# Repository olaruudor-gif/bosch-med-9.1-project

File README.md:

Started making a pcb for replacing the oem bosch ecu to make it tunable with tunerstudio and rusefi code.

Please feel free to use my files to continue my work.

No rights reserved.

Just a simple thanks, and I am happy!

It's all MAGIC

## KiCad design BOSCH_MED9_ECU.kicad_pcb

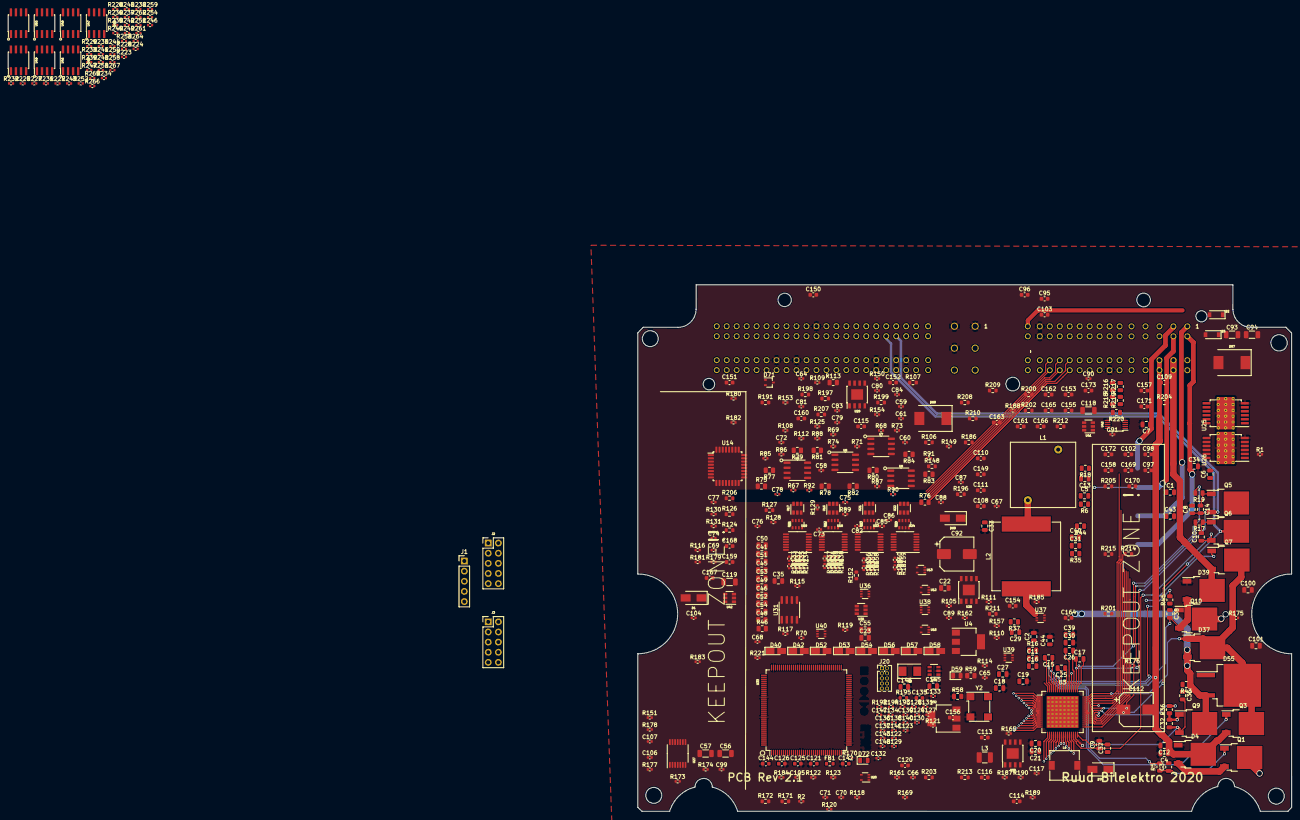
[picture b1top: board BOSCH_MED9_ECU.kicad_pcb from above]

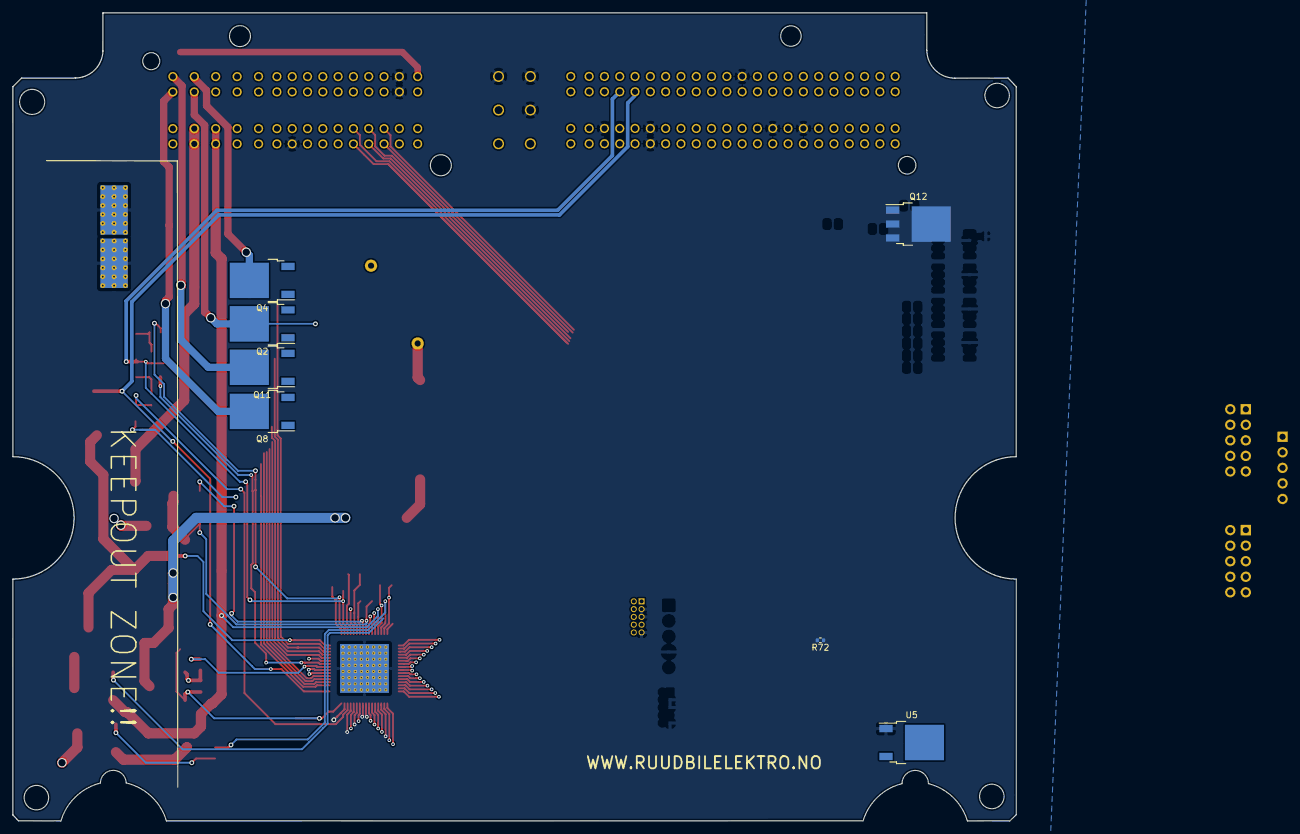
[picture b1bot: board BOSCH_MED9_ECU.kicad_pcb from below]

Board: 4 copper layers, 163.9 x 132.0 mm, 466 parts (7 on the bottom side), 339 nets.

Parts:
C1, C4, C6, C7, C8, C12, C30, C34, C39, C43: 4700pF; C_0805_2012Metric
C2, C9, C35, C36, C37, C44: 330pF; C_0805_2012Metric
C3, C5, C10, C11, C13, C14, C29, C31, C38, C40, C55: 1000pF; C_0805_2012Metric
C15, C16, C17, C25, C26: 0.33uF; C_0805_2012Metric
C18: 4.7uF; C_0805_2012Metric
C19, C20, C22, C23: 0.1uF; C_0805_2012Metric
C21: 1uF; C_0805_2012Metric
C27, C33: 220nF; C_0805_2012Metric
C32: 470pF; C_0805_2012Metric
C41, C45: 0.22uF; C_0805_2012Metric
C46, C49, C51, C53, C145: 100nF; C_0805_2012Metric
C48, C50, C52, C54: 10nF; R_0805_2012Metric
C56, C57, C93, C94, C118, C119: 10uF; C_1206_3216Metric
C58, C59, C60, C61, C65, C69, C127, C128, C129, C130, C131, C132, C133, C134, C136, C138, C139, C140, C141, C143, C147, C148: 100nF; C_0402_1005Metric
C64: 220pf; C_0402_1005Metric
C66, C67, C70, C71: 33nF; C_0402_1005Metric
C68: 1nF; C_0402_1005Metric
C72, C73, C74, C75, C76, C77, C78, C79, C80, C81, C82, C83, C84, C85, C86, C87, C88, C89, C90, C91, C99, C122, C137: 10nF; C_0402_1005Metric
C92: 220uF; CP_Elec_8x10
C95, C96, C97, C98, C114, C169, C171: 10nF; C_0603_1608Metric
C100, C101: 3.3nF; C_0805_2012Metric
C102, C103: 680pF; C_0603_1608Metric
C104, C105: 330p; C_0402_1005Metric
C106, C107: 47pF; C_0402_1005Metric
C108, C109, C111, C113, C115, C121, C135, C144: 1uF; C_0603_1608Metric
C110, C120, C142: 4.7uF; C_0603_1608Metric
C112: 68uF; CP_Elec_8x10
C116, C173: 100nF; C_0603_1608Metric
C117: 270pF; C_0402_1005Metric
C123, C124: 4.7pF; C_0402_1005Metric
C125, C126: 2.2uF; C_0603_1608Metric
C146: 22uF; C_0805_2012Metric
C149, C150, C151, C152, C153, C154, C155, C156, C157, C158, C159, C160, C161, C162, C163, C164, C165, C166, C167, C168, C170, C172: 1nF; C_0603_1608Metric
D1: SS54; D_SMA
D2, D3: B5819W; D_SOD-123
D4, D39: SBR10200CTL; TO-252-2
D37: FFD10UP20S; TO-252-2
D40, D42, D52, D53, D54, D56, D57, D58: 5.7V; D_MicroMELF_Handsoldering
D55: STTH802G-TR; TO-263-2
D59: LED_Small; LED_0805_2012Metric
D67, D68: SM15T33CA; D_SMC
D69, D70: D_Schottky; D_SMA
D71: PESD1CAN-UX; SOT-323_SC-70
D72: LED GREEN; LED_0805_2012Metric
FB1: FILTER; R_0603_1608Metric
J1: Conn_01x05; PinHeader_1x05_P2.54mm_Vertical
J2, J3: Conn_01x10; PinHeader_2x05_P2.54mm_Vertical
J20: Conn_02x05_Odd_Even; PinHeader_2x05_P1.27mm_Vertical
L1: 6uH; L_Radial_L16.1mm_W16.1mm_Px7.62mm_Py12.70mm_Pulse_LP-44
L2: 10uH; L_Vishay_IHLP-6767
L3: 2.2uF; L_1210_3225Metric
L4: 10uF; L_7.3x7.3_H3.5
Q1, Q2, Q3, Q4, Q5, Q6, Q7, Q8, Q9, Q10, Q11: BUK9230-100B; TO-252-2
Q12: RFD16N05LSM9A; TO-252-3_TabPin2
R1, R2: 10k; R_0402_1005Metric
R5, R6, R16, R17, R18, R19, R35, R36, R37, R44, R45, R58: 10R; R_0805_2012Metric
R43, R46: 5.1R; R_0805_2012Metric
R59: 1k; R_0805_2012Metric
R67, R68, R69, R70, R71, R72, R73, R74, R85, R86, R87, R88, R89, R90, R91, R92, R105, R111, R115, R117, R121, R122, R149, R185, R187, R188, R192, R193, R226, R231, R232, R235, R236, R237, R238, R239, R240, R241, R242, R243, R244, R245, R246, R247, R248, R249, R250, R251, R258, R259, R261, R262, R264, R265, R266, R267: 10K; R_0402_1005Metric
R75: 0R; R_0805_2012Metric
R76, R220: DNP; R_0805_2012Metric
R77, R78, R79, R80, R81, R82, R83, R84: 100R; R_0805_2012Metric
R106: 220R; R_0603_1608Metric
R107: 82.5R; R_0603_1608Metric
R108, R116, R119, R175, R176, R181, R182, R194: 100K; R_0402_1005Metric
R109, R125, R128, R129, R130, R131, R150, R151, R153, R154, R177, R178: 470K; R_0402_1005Metric
R110: 21.6K; R_0402_1005Metric
R112, R221: 4.7K; R_0402_1005Metric
R113: 61.9R; R_0805_2012Metric
R114, R123: 6.8K; R_0402_1005Metric
R118, R120, R132, R133, R134, R135, R136, R137, R138, R139, R155, R156, R157, R158, R159, R160, R161, R162, R222, R223, R224, R225, R227, R228, R229, R230, R233, R234, R252, R253, R254, R255: 1K; R_0402_1005Metric
R124, R126, R127, R152: 2.7K; R_0603_1608Metric
R140, R141, R142, R143, R144, R145, R146, R147, R163, R164, R165, R166, R167, R168, R169, R170: 1.5K; R_0402_1005Metric
R148: 39K; R_0603_1608Metric
R171, R172: 10K; R_0603_1608Metric
R173, R174: 22k; R_0402_1005Metric
R179, R180, R189: 12K; R_0402_1005Metric
R183, R184: 33K; R_0402_1005Metric
R186: 10Hms; R_0603_1608Metric
R190: 68K; R_0402_1005Metric
R191: 120R; R_0603_1608Metric
R195: 680R; R_0603_1608Metric
R196, R197, R198, R199, R200, R201, R202, R203, R204, R205: 2.2K; R_0603_1608Metric
R206, R207, R208, R209, R210, R211, R212, R213, R214, R215: 3.3K; R_0603_1608Metric
R216, R217, R218, R219: 5K; R_0805_2012Metric
RN1, RN2, RN3, RN4: 10K; R_Array_Convex_4x0603
U1: BOSCH_94-PIN; BOSCH_94_PIN
U2: BOSCH_60-PIN; BOSCH_60_PIN
U3: MC33816; HTQFP-64-1EP_10x10mm_P0.5mm_EP8x8mm_Mask4.4x4.4mm_ThermalVi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
U4: AMS1117-3.3; SOT-223
U5: NCP1117-5.0_TO252; TO-252-2
U6, U7, U8, U9: TC4427; SO-8_3.9x4.9mm_P1.27mm
U12, U13, U15, U20: TS5A3166DCKR; SOT-353_SC-70-5
U14: CJ125; LQFP-32_7x7mm_P0.8mm
U16, U17, U21, U22, U34, U35, U41, U42: SRV05-4; SOT-23-6
U18, U19, U23, U24, U27: MCP6004T-I/ST; TSSOP-14_4.4x5mm_P0.65mm
U25, U26: IFX9201SGAUMA1; Infineon_PG-DSO-12-9_ThermalVias
U28, U29: TLS115; Infineon_PG-DSO-8-43
U30: LMR14020; Infineon_PG-DSO-8-43
U31: TJA1051T-3; SOIC-8_3.9x4.9mm_P1.27mm
U32: AMS1117-3.3; SOT-223-3_TabPin2
U33: STM32F767ZIT6; LQFP-144_20x20mm_P0.5mm
U36, U37, U38, U39, U40: 74LVC2G17; SOT-363_SC-70-6
U43: MAX9924; MSOP-10_3x3mm_P0.5mm
U44, U45, U46, U47, U48, U49, U50: 511-VNLD5160TR-E; PowerIntegrations_SO-8
X1: 8MHz; Crystal_SMD_5032-2Pin_5.0x3.2mm
Y2: 1MHz; Oscillator_SMD_Diodes_FN-4Pin_7.0x5.0mm

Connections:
+3V3: C23.1, C55.1, C120.1, C127.2, C128.2, C129.2, C130.2, C131.2, C132.2, C133.2, C134.2, C136.2, C138.2, C139.2, C140.2, C141.2, C144.2, C145.1, C146.1, D72.2, FB1.1, J3.4, J20.1, R1.1, R2.1, R171.2, R172.2, R173.2, R193.2, R221.1, U3.17, U25.2, U26.2, U27.4, U31.5, U32.2, U33.6, U33.17, U33.30, U33.39, U33.52, U33.62, U33.72, U33.84, U33.95, U33.108, U33.121, U33.131, U33.143, U33.144, Y2.4
+5V: C22.1, C66.2, C80.1, C81.1, C90.1, C91.1, C117.1, C118.1, C119.1, C142.2, C143.1, C173.1, J3.1, L4.2, R76.1, R115.2, R126.2, R127.2, R185.2, R188.2, R190.2, R196.1, R197.1, R198.1, R199.1, R200.1, R201.1, R202.1, R203.1, R204.1, R205.1, RN4.1, U3.21, U12.5, U13.5, U14.5, U14.18, U14.19, U15.2, U15.5, U16.5, U17.5, U18.4, U19.4, U20.2, U20.5, U21.5, U22.5, U23.4, U24.4, U28.5, U31.3, U32.3, U35.5, U36.5, U37.5, U38.5, U39.5, U40.5, U41.5, U42.5, U43.10
/5V1: C109.1, U2.37, U28.1
/5V2: C115.1, U1.58, U1.63, U1.80, U2.26, U29.9
/5V_Ext: C58.1, C59.1, C60.1, C61.1, R75.1, R76.2, R242.2, R243.1, R244.2, R245.1, R246.2, R247.1, R248.2, R249.1, R250.2, R251.1, R264.2, R265.1, R266.2, R267.1, U6.6, U7.6, U8.6, U9.6
/12V: C67.2, C108.1, C111.1, D69.1, J3.3, L3.1, R148.2, R186.1, U14.30, U28.7, U28.8
/12V_FROM_MAIN_RELAY: C92.1, C93.2, C94.2, D2.1, D3.1, D67.1, J3.8, U25.4, U26.4
/12V_IGN: D68.1, D69.2
/12V_SWITCH_PROT: C56.1, D1.1, U5.3
/AC-COMP: R251.2, U48.6
/AC-REQ: C154.1, R201.2, R211.2
/ACC-PEDAL-1: R150.1, RN3.1, U1.79
/ACC-PEDAL-2: R154.1, RN4.4, U1.57
/ADC8_BIAS: U15.4, U33.77
/ADC14_BIAS: U20.4, U33.11
/ADC/ADC_11_MCU: R157.2, R165.1
/AN-TEMP-1: R124.1, RN2.1
/AN-VOLT-2: J1.4, R151.1, RN3.3
/AN-VOLT-3: R130.1, RN1.3
/AN_VOLT_1: R131.1, RN1.4
/AnOut1: R132.2, R140.1, U33.26
/AnOut2: R133.2, R141.1, U33.27
/AnOut3: R134.2, R142.1, U33.28
/AnOut4: R135.2, R143.1, U33.29
/AnOut5: R136.2, R144.1, U33.47
/AnOut6: R137.2, R145.1, U33.46
/AnOut7: R138.2, R146.1, U33.45
/AnOut8: R139.2, R147.1, U33.44
/AnOut9: R155.2, R163.1, U33.43
/AnOut10: R156.2, R164.1, U33.42
/AnOut12: R158.2, R166.1, U33.41
/AnOut13: R159.2, R167.1, U33.40
/AnOut14: R160.2, R168.1, U33.37
/BOOST_VALVE: R243.2, U44.6
/BRAKE-PEDAL: C149.1, R196.2, R206.2
/BRAKE-PEDAL-2: C156.1, R203.2, R213.2
/BRAKE-RELAY: R244.1, U1.31, U45.8
/CAM_1: C157.1, R204.2, R214.2
/CAM_1_MCU: U33.96, U40.6
/CAM_2: C158.1, R205.2, R215.2
/CAM_2_MCU: U33.93, U40.4
/CANH: D71.2, R191.1, U1.68, U1.90, U31.7
/CANL: D71.1, R191.2, U1.67, U1.89, U31.6
/CLT_SENSOR: R126.1, RN1.1
/CLUTCH-PEDAL: C150.1, R197.2, R207.2, U1.41
/COIL-1: R82.1, R89.2, U2.58
/COIL-2: R77.1, R85.2, U2.43
/COIL-3: R80.1, R87.2, U2.56
/COIL-4: R78.1, R92.2, U2.41
/COIL-5: R81.1, R88.2, U2.57
/COIL-6: R79.1, R86.2, U2.42
/COIL-7: R83.1, R90.2
/COIL-8: R84.1, R91.2
/CRANK: C172.1, R221.2, U33.86, U43.7
/CRIUSE-SET: C152.1, R199.2, R209.2
/CRNK+: R217.2, U2.51
/CRNK-: R216.2, U2.36
/CRUISE-SW: C153.1, R200.2, R210.2
/CS_LSU: U14.17, U33.66
/DI1: U33.54, U36.6
/DI2: U33.55, U36.4
/DI3: U33.97, U37.6
/DI4: U33.49, U37.4
/DI5: U33.56, U38.6
/DI6: U33.57, U38.4
/DI7: U33.50, U39.6
/DI8: U33.53, U39.4
/DIGITAL_GP: C155.1, R202.2, R212.2
/E-Throttle/ETB_1_DIR: U25.1, U33.99
/E-Throttle/ETB_1_DIS: R171.1, U25.11, U33.124
/E-Throttle/ETB_1_PWM: U25.12, U33.100
/E-Throttle/ETB_2_DIR: U26.1, U33.98
/E-Throttle/ETB_2_DIS: R172.1, U26.11, U33.122
/E-Throttle/ETB_2_PWM: U26.12, U33.123
/ECT-SENSOR-2: R152.1, RN4.3, U1.12
/ENGINE-RELAY: R246.1, U1.69, U46.8
/ETB_1+: C95.2, U2.15, U25.5
/ETB_1-: C96.1, U2.30, U25.7
/ETB_2+: C97.2, U26.5
/ETB_2-: C98.1, U26.7
/EXH-CAM: D3.2, R249.2, U47.6
/FAN_CONTROL: R247.2, U46.6
/FUEL-PUMP: R245.2, U45.6
/FUEL-PUMP+: C8.1, C14.2, C17.1, Q5.3, U1.32, U3.51
/FUEL-PUMP-: C6.1, Q6.2, U1.33, U3.33
/GPIOF_2: J2.2, U33.12
/HGATE-LSU: Q12.1, R121.2, U14.4, U33.64
/IAT-SENSOR: U1.13, U2.13
/IAT_SENSOR: R127.1, RN2.3
/IGN1: R67.1, U6.2, U33.115
/IGN2: R72.2, U6.4, U33.114
/IGN3: R68.1, U7.2, U33.119
/IGN4: R71.2, U7.4, U33.118
/IGN5: R69.1, U8.2, U33.117
/IGN6: R74.2, U8.4, U33.116
/IGN7: R73.1, U9.2, U33.92
/IGN8: R70.2, U9.4, U33.91
/INJECTOR-1: C7.1, Q4.2, U2.2, U3.38
/INJECTOR-2: C1.1, Q2.2, U2.17, U3.37
/INJECTOR-3: C34.1, Q8.2, U2.16, U3.36
/INJECTOR-4: C43.1, Q11.2, U2.1, U3.35
/INJECTOR_DRIVERS/INJ_IN_1: R222.2, U33.140
/INJECTOR_DRIVERS/INJ_IN_2: R223.2, U33.141
/INJECTOR_DRIVERS/INJ_IN_3: R233.2, U33.142
/INJECTOR_DRIVERS/INJ_IN_4: R234.2, U33.1
/INJECTOR_DRIVERS/INJ_IN_5: R224.2, U33.2
/INJECTOR_DRIVERS/INJ_IN_6: R225.2, U33.3
/INJECTOR_DRIVERS/INJ_IN_7: R227.2, U33.137
/INJECTOR_DRIVERS/INJ_IN_8: R228.2, U33.139
/INJECTOR_DRIVERS/LS_IN_9: R229.2, U33.127
/INJECTOR_DRIVERS/LS_IN_10: R230.2, U33.128
/INJECTOR_DRIVERS/LS_IN_11: R252.2, U33.125
/INJECTOR_DRIVERS/LS_IN_12: R253.2, U33.126
/INJECTOR_DRIVERS/LS_IN_13: R254.2, U33.129
/INJECTOR_DRIVERS/LS_IN_14: R255.2, U33.132
/INJECTOR_PWR_BNK_1_1: C4.1, C11.2, C12.1, C16.2, D4.2, Q3.3, U2.33, U2.48, U3.60
/INJECTOR_PWR_BNK_2_1: C26.2, C29.2, C30.1, C39.1, D39.2, Q7.3, U2.32, U2.47, U3.54
/INJECTOR_PWR_BNK_3_1: U2.31, U2.46
/INT-CAM: D2.2, R266.1, U50.8
/L9637_L: J3.7, U33.13
/LSU1_HEATER: Q12.2, R114.1, U1.51
/LSUIA1: R109.1, R113.1, U1.81, U14.2
/LSUIP1: R113.2, U1.60, U14.32
/LSUUN1: C64.1, R108.2, U1.82, U14.31
/LSUVM1: R107.1, U1.61, U14.20
/LS_OUT_1: R242.1, U44.8
/LS_OUT_2: R267.2, U50.6
/LS_OUT_3: R265.2, U49.6
/LS_OUT_4: R250.1, U48.8
/LS_OUT_5: R248.1, U47.8
/MAF-SENSOR: R153.1, RN3.4, U1.85
/MAP-SENSOR: R128.1, RN1.2, U1.38
/MCU/D+: U33.104, U34.1
/MCU/D-: U33.103, U34.3
/MCU/NRST: J20.10, R193.1, U33.25
/MCU/PB6: U31.1, U33.136
/MCU/PB12: U31.4, U33.73
/MCU/SWCLK: J20.4, U33.109
/MCU/SWDIO: J20.2, U33.105
/MCU/Vbus: C148.2, U33.101, U34.5
/MCU/shield: C147.1, R194.1
/O2_input_CJ125/4.2_4.9: R105.2, U12.4, U13.4, U33.65
/O2_input_CJ125/COM: R106.1, R107.2, U12.2
/O2_input_CJ125/NO: R106.2, U12.1, U14.8
/POWER SUPPLY/5V_SENSOR_1_PG: R185.1, U28.4
/PT2000/BANK1_BAT: C3.2, C15.2, D4.3, Q1.3, U3.63
/PT2000/BANK2_BAT: C25.2, C38.2, D39.3, Q10.3, U3.57
/PT2000/CLK: U3.1, Y2.3
/PT2000/G_HB1_BAT: R5.2, U3.62
/PT2000/G_HB1_BST: R16.2, U3.59
/PT2000/G_HB2_BAT: R45.2, U3.56
/PT2000/G_HB2_BST: R37.2, U3.53
/PT2000/G_LS6: R19.2, U3.50
/PT2000/G_L_BOOST: R36.2, U3.41
/PT2000/G_L_INJ1: R18.2, U3.47
/PT2000/G_L_INJ2: R6.2, U3.46
/PT2000/G_L_INJ3: R35.2, U3.45
/PT2000/G_L_INJ4: R44.2, U3.44
/PT2000/G_PUMP: R17.2, U3.42
/PT2000/P_B1_SENSE: C2.1, C5.1, C13.1, Q2.3, Q4.3, U3.26
/PT2000/P_B2_SENSE: C31.1, C40.1, C44.1, Q8.3, Q11.3, U3.28
/PT2000/P_SENSE_BOOST: C32.1, C35.1, C36.2, C37.2, C41.2, C45.2, C46.2, C48.2, C49.2, C50.2, C51.2, C52.2, C53.2, C54.2, Q9.3, U3.32
/PT2000/P_SENSE_PUMP: C9.1, C10.1, Q6.3, U3.30
/PT2000/VCC2P5: C20.1, C21.1, U3.20
/PT2000/VCCP: C18.1, C19.1, U3.40
/PT2000/Vbat: C27.1, L1.2, Q1.2, Q5.2, Q10.2, U3.39
/PT2000/Vboost: C41.1, C45.1, C46.1, C48.1, C49.1, C50.1, C51.1, C52.1, C53.1, C54.1, D37.1, D37.2, D40.1, D55.2, Q3.2, Q7.2, R46.1, U3.48
/PT2000/Vbuck: D37.3, D55.3, L2.1, Q9.2, R43.1
/PT2000/Vpwr: C33.1, L1.1, L2.2
/SCK-LSU: U14.13, U33.74
/SD_CS: J1.5, U33.18
/SI-LSU: U14.15, U33.76
/SO-LSU: R119.2, U14.14, U33.75
/SPEED-SIGNAL: C151.1, R198.2, R208.2, U1.71
/SPI5_MISO: J1.1, U33.20
/SPI5_MOSI: J1.2, U33.21
/SPI5_SCK: J1.3, U33.19
/STARTER_RELAY: U1.52, U1.74
/THERMOSTAT: R264.1, U1.8, U49.8
/TPS_MAIN: R125.1, RN2.2
/TPS_SUB: R129.1, RN2.4
/UA-LSU: R122.1, R123.1, U33.36
/UART4_RX: J2.8, U33.112
/UART4_TX: J2.10, U33.111
/UART7_CTS: J2.6, U33.63
/UART7_RTS: J2.4, U33.60
/UART7_RX: J3.9, U33.59
/UART7_TX: J3.10, U33.58
/UBHR: U1.3, U1.5, U1.6
/UBR_MCU: R161.2, R169.1, U33.34
/UR-LSU: C70.1, R118.1, U33.35
/USART3_RX: J3.5, U33.70
/USART3_TX: J3.6, U33.69
/Vref: C121.2, C122.2, R162.2, R170.1, U33.32
/knock/FILTERED_1: C104.2, U27.6, U27.7, U33.14
/knock/FILTERED_2: C105.2, U27.8, U27.9, U33.15
/knock/V_mid: C99.2, R173.1, R174.1, U27.3, U27.12
GND: C1.2, C2.2, C4.2, C6.2, C7.2, C8.2, C9.2, C12.2, C18.2, C19.2, C20.2, C21.2, C22.2, C23.2, C27.2, C30.2, C33.2, C34.2, C35.2, C39.2, C43.2, C44.2, C55.2, C56.2, C57.2, C58.2, C59.2, C60.2, C61.2, C64.2, C66.1, C67.1, C68.2, C69.1, C70.2, C71.1, C72.2, C73.2, C74.2, C75.2, C76.2, C77.2, C78.2, C79.2, C80.2, C81.2, C82.2, C83.2, C84.2, C85.2, C86.2, C87.2, C88.2, C89.2, C90.2, C91.2, C92.2, C93.1, C94.1, C95.1, C96.2, C97.1, C98.2, C99.1, C102.1, C103.1, C106.1, C107.1, C108.2, C109.2, C110.2, C111.2, C112.2, C113.2, C114.2, C115.2, C118.2, C119.2, C120.2, C121.1, C122.1, C123.2, C124.2, C125.2, C126.2, C127.1, C128.1, C129.1, C130.1, C131.1, C132.1, C133.1, C134.1, C135.1, C136.1, C137.1, C138.1, C139.1, C140.1, C141.1, C142.1, C143.2, C144.1, C145.2, C146.2, C147.2, C148.1, C149.2, C150.2, C151.2, C152.2, C153.2, C154.2, C155.2, C156.2, C157.2, C158.2, C159.2, C160.2, C161.2, C162.2, C163.2, C164.2, C165.2, C166.2, C167.2, C168.2, C169.1, C171.2, C172.2, C173.2, D4.1, D39.1, D59.1, D67.2, D68.2, D70.2, D71.3, J3.2, J20.3, J20.5, J20.9, Q12.3, R58.1, R67.2, R68.2, R69.2, R70.1, R71.1, R72.1, R73.2, R74.1, R85.1, R86.1, R87.1, R88.1, R89.1, R90.1, R91.1, R92.1, R105.1, R117.1, R119.1, R121.1, R122.2, R125.2, R128.2, R129.2, R130.2, R131.2, R140.2, R141.2, R142.2, R143.2, R144.2, R145.2, R146.2, R147.2, R149.2, R150.2, R151.2, R153.2, R154.2, R163.2, R164.2, R165.2, R166.2, R167.2, R168.2, R169.2, R170.2, R174.2, R187.2, R189.2, R192.2, R194.2, R195.1, R226.1, R231.1, R232.1, R235.1, R236.1, R237.1, R238.1, R239.1, R240.1, R241.1, R258.1, R259.1, R261.1, R262.1, U1.1, U1.2, U1.4, U1.53, U1.54, U1.56, U1.64, U1.66, U1.76, U1.78, U2.14, U2.29, U2.52, U3.19, U3.24, U3.25, U3.27, U3.29, U3.31, U3.65, U5.1, U6.3, U7.3, U8.3, U9.3, U12.3, U13.3, U14.28, U14.29, U15.3, U16.2, U17.2, U18.11, U19.11, U20.3, U21.2, U22.2, U23.11, U24.11, U25.6, U25.13, U26.6, U26.13, U27.11, U28.3, U28.9, U30.7, U30.9, U31.2, U31.8, U32.1, U33.16, U33.31, U33.38, U33.51, U33.61, U33.83, U33.94, U33.107, U33.120, U33.130, U34.2, U35.2, U36.2, U37.2, U38.2, U39.2, U40.2, U41.2, U42.2, U43.4, U43.5, U43.6, U43.9, U44.5, U44.7, U45.5, U45.7, U46.5, U46.7, U47.5, U47.7, U48.5, U48.7, U49.5, U49.7, U50.5, U50.7, Y2.2
unnamed: C3.1, Q1.1, R5.1
unnamed: C5.2, Q2.1, R6.1
unnamed: C10.2, Q6.1, R17.1
unnamed: C11.1, Q3.1, R16.1
unnamed: C13.2, Q4.1, R18.1
unnamed: C14.1, Q5.1, R19.1
unnamed: C15.1, U3.61
unnamed: C16.1, U3.58
unnamed: C17.2, U3.49
unnamed: C25.1, U3.55
unnamed: C26.1, U3.52
unnamed: C29.1, Q7.1, R37.1
unnamed: C31.2, Q8.1, R35.1
unnamed: C32.2, Q9.1, R36.1
unnamed: C36.1, R43.2
unnamed: C37.1, R46.2
unnamed: C38.1, Q10.1, R45.1
unnamed: C40.2, Q11.1, R44.1
unnamed: C57.1, R75.2, U5.2
unnamed: C65.1, R111.1
unnamed: C65.2, U14.11
unnamed: C68.1, R115.1, U14.7
unnamed: C69.2, R116.2, U14.26
unnamed: C71.2, R120.1, R123.2
unnamed: C72.1, RN1.5, U17.6, U19.10
unnamed: C73.1, RN2.5, U16.6, U18.10
unnamed: C74.1, RN1.6, U17.1, U19.12
unnamed: C75.1, RN2.6, U16.1, U18.12
unnamed: C76.1, RN1.7, U17.3, U19.3
unnamed: C77.1, RN2.7, U16.3, U18.3
unnamed: C78.1, RN1.8, U17.4, U19.5
unnamed: C79.1, RN2.8, U16.4, U18.5
unnamed: C82.1, RN3.5, U21.6, U23.10
unnamed: C83.1, RN3.6, U21.1, U23.12
unnamed: C84.1, RN3.7, U21.3, U23.3
unnamed: C85.1, RN3.8, U21.4, U23.5
unnamed: C86.1, RN4.5, U22.6, U24.10
unnamed: C87.1, RN4.6, U22.1, U24.12
unnamed: C88.1, RN4.7, U24.3
unnamed: C89.1, RN4.8, U24.5
unnamed: C100.1, R175.2
unnamed: C101.1, R176.2
unnamed: C102.2, R179.1, R181.2
unnamed: C103.2, R180.1, R182.2
unnamed: C104.1, R181.1, R183.2
unnamed: C105.1, R182.1, R184.2
unnamed: C106.2, R183.1, U27.5
unnamed: C107.2, R184.1, U27.10
unnamed: C110.1, R186.2
unnamed: C112.1, C113.1, L3.2, U30.2, U30.3
unnamed: C114.1, U30.6
unnamed: C116.1, U30.1
unnamed: C116.2, D70.1, L4.1, U30.8
unnamed: C117.2, R189.1, R190.1, U30.5
unnamed: C123.1, U33.23, X1.2
unnamed: C124.1, U33.24, X1.1
unnamed: C125.1, U33.71
unnamed: C126.1, U33.106
unnamed: C135.2, C137.2, FB1.2, U33.33
unnamed: C159.1, R206.1, U35.1, U36.1
unnamed: C160.1, R207.1, U35.3, U36.3
unnamed: C161.1, R208.1, U37.1, U41.1
unnamed: C162.1, R209.1, U37.3, U41.3
unnamed: C163.1, R210.1, U35.4, U38.1
unnamed: C164.1, R211.1, U35.6, U38.3
unnamed: C165.1, R212.1, U39.1, U41.6
unnamed: C166.1, R213.1, U39.3, U41.4
unnamed: C167.1, R214.1, U40.1, U42.6
unnamed: C168.1, R215.1, U40.3, U42.4
unnamed: C169.2, C170.1, R218.1, R220.2, U43.2
unnamed: C170.2, C171.1, R219.1, R220.1, U43.1
unnamed: D40.2, D42.1
unnamed: D42.2, D52.1
unnamed: D52.2, D53.1
unnamed: D53.2, D54.1
unnamed: D54.2, D56.1
unnamed: D56.2, D57.1
unnamed: D57.2, D58.1
unnamed: D58.2, U4.3
unnamed: D59.2, R59.1, U4.2
unnamed: D72.1, R195.2
unnamed: R58.2, Y2.1
unnamed: R59.2, U4.1
unnamed: R77.2, U6.7
unnamed: R78.2, U6.5
unnamed: R79.2, U7.7
unnamed: R80.2, U7.5
unnamed: R81.2, U8.7
unnamed: R82.2, U8.5
unnamed: R83.2, U9.7
unnamed: R84.2, U9.5
unnamed: R108.1, R109.2, R112.1, U14.22
unnamed: R110.1, R111.2, U13.2
unnamed: R110.2, U13.1, U14.10
unnamed: R112.2, U14.21
unnamed: R114.2, U14.6
unnamed: R116.1, U14.27
unnamed: R117.2, U14.3
unnamed: R118.2, U14.12
unnamed: R120.2, U14.23
unnamed: R124.2, U15.1
unnamed: R132.1, U19.8, U19.9
unnamed: R133.1, U19.13, U19.14
unnamed: R134.1, U19.1, U19.2
unnamed: R135.1, U19.6, U19.7
unnamed: R136.1, U18.8, U18.9
unnamed: R137.1, U18.13, U18.14
unnamed: R138.1, U18.1, U18.2
unnamed: R139.1, U18.6, U18.7
unnamed: R148.1, R149.1, RN4.2
unnamed: R152.2, U20.1
unnamed: R155.1, U23.8, U23.9
unnamed: R156.1, U23.13, U23.14
unnamed: R157.1, U23.1, U23.2
unnamed: R158.1, U23.6, U23.7
unnamed: R159.1, U24.8, U24.9
unnamed: R160.1, U24.13, U24.14
unnamed: R161.1, U24.1, U24.2
unnamed: R162.1, U24.6, U24.7
unnamed: R175.1, R177.2, U27.2
unnamed: R176.1, R178.2, U27.13
unnamed: R177.1, R179.2, U27.1
unnamed: R178.1, R180.2, U27.14
unnamed: R187.1, U30.4
unnamed: R192.1, U33.138
unnamed: R216.1, R218.2
unnamed: R217.1, R219.2
unnamed: R222.1, R231.2, U44.1
unnamed: R223.1, R226.2, U44.3
unnamed: R224.1, R237.2, U45.1
unnamed: R225.1, R232.2, U45.3
unnamed: R227.1, R238.2, U46.1
unnamed: R228.1, R235.2, U46.3
unnamed: R229.1, R240.2, U47.1
unnamed: R230.1, R236.2, U47.3
unnamed: R233.1, R241.2, U48.1
unnamed: R234.1, R239.2, U48.3
unnamed: R252.1, R261.2, U49.1
unnamed: R253.1, R258.2, U49.3
unnamed: R254.1, R262.2, U50.1
unnamed: R255.1, R259.2, U50.3
